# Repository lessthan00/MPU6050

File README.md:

# MPU6050

[MPU6050](https://www.jlc-smt.com/lcsc/detail?componentCode=C24112)
姿态传感器/陀螺仪

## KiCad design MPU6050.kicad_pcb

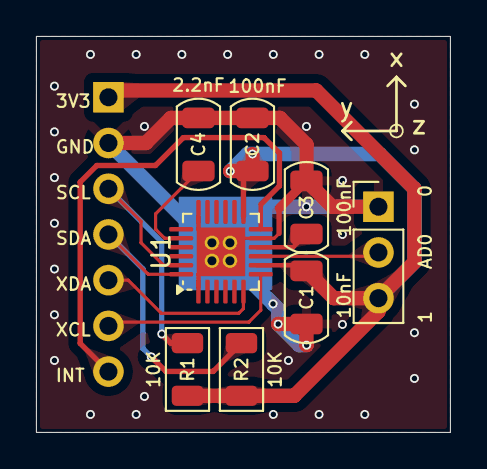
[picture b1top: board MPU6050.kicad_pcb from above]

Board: 2 copper layers, 23.0 x 22.0 mm, 9 parts (1 on the bottom side), 10 nets.

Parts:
C1: 10nF; C_1206_3216Metric
C2, C3: 100nF; C_1206_3216Metric
C4: 2.2nF; C_1206_3216Metric
J1: Conn_01x03; PinHeader_1x03_P2.54mm_Vertical
J2: Conn_01x07; PinHeader_1x07_P2.54mm_Vertical
R1, R2: 10K; R_1206_3216Metric
U1: MPU-6050; QFN-24-1EP_4x4mm_P0.5mm_EP2.7x2.7mm_ThermalVias

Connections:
+3.3V: C1.1, C2.1, J1.3, J2.1, R1.1, R2.1, U1.8 (VDDIO), U1.13 (VDD)
/AUX_CL: J2.6, U1.7 (AUX_SCL)
/AUX_DA: J2.5, U1.6 (AUX_SDA)
/IIC_AD0: J1.2, U1.9 (AD0)
/IIC_SCL: J2.3, R1.2, U1.23 (SCL)
/IIC_SDA: J2.4, R2.2, U1.24 (SDA)
/INT: J2.7, U1.12 (INT)
GND: C1.2, C2.2, C3.1, C4.2, J1.1, J2.2, U1.1 (CLKIN), U1.11 (FSYNC), U1.18 (GND), U1.25 (GND)
unnamed: C4.1, U1.20 (CPOUT)
unnamed: C3.2, U1.10 (REGOUT)
